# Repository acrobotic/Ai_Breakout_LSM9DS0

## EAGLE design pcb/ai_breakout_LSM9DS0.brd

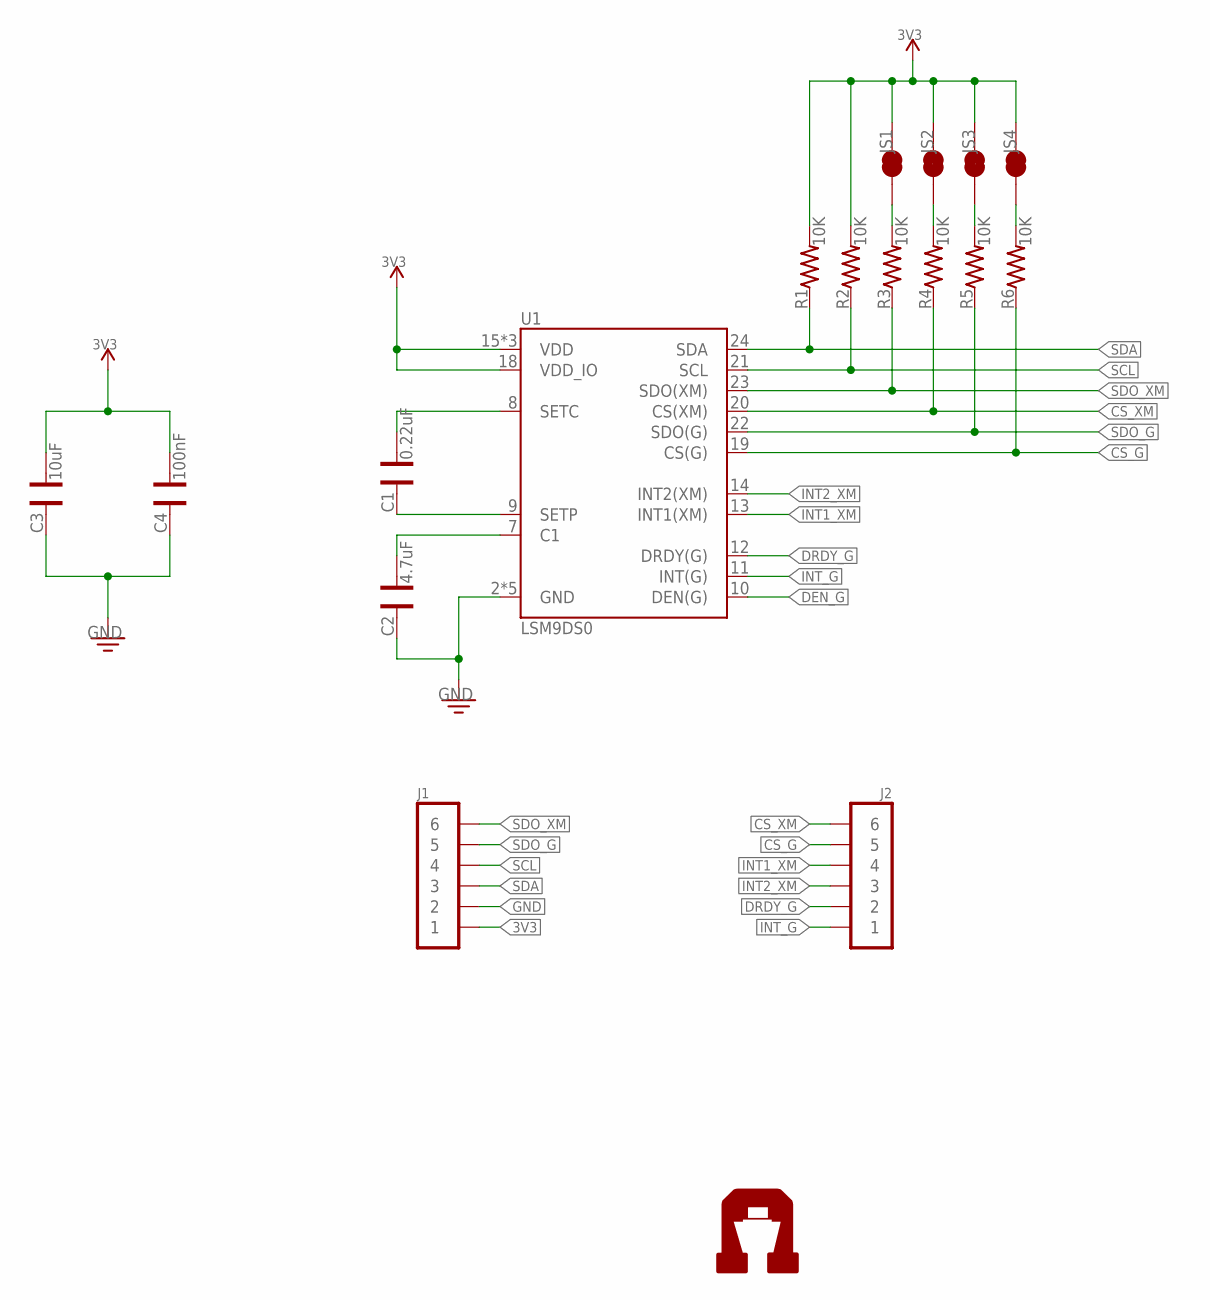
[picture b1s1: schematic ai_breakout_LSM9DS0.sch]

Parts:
C1: 0.22uF; CAP-0603
C2: 4.7uF; CAP-0603
C3: 10uF; CAP-0603
C4: 100nF; CAP-0603
J1: 1X06
J2: 1X06NOFIRST; 1X06-NOFIRST
JS1, JS2, JS3, JS4: 1X02-SJ-NCT
R1, R2, R3, R4, R5, R6: 10K; RES-0603
U1: LSM9DS0; LGA-24
U$4: AI-LOGOXS; AI-LOGO-XS

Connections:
3V3: C3.1, C4.1, J1.1, JS1.2, JS2.2, JS3.2, JS4.2, R1.2, R2.2, U1.15 (VDD), U1.16 (VDD), U1.17 (VDD), U1.18 (VDD_IO)
CS_G: J2.5, R6.1, U1.19 (CS(G))
CS_XM: J2.6, R4.1, U1.20 (CS(XM))
DEN_G: U1.10 (DEN(G))
DRDY_G: J2.2, U1.12 (DRDY(G))
GND: C2.2, C3.2, C4.2, J1.2, U1.2 (GND), U1.3 (GND), U1.4 (GND), U1.5 (GND), U1.6 (GND)
INT1_XM: J2.4, U1.13 (INT1(XM))
INT2_XM: J2.3, U1.14 (INT2(XM))
INT_G: J2.1, U1.11 (INT(G))
unnamed: C1.1, U1.8 (SETC)
unnamed: C1.2, U1.9 (SETP)
unnamed: C2.1, U1.7 (C1)
unnamed: JS1.1, R3.2
unnamed: JS2.1, R4.2
unnamed: JS3.1, R5.2
unnamed: JS4.1, R6.2
SCL: J1.4, R2.1, U1.21 (SCL)
SDA: J1.3, R1.1, U1.24 (SDA)
SDO_G: J1.5, R5.1, U1.22 (SDO(G))
SDO_XM: J1.6, R3.1, U1.23 (SDO(XM))

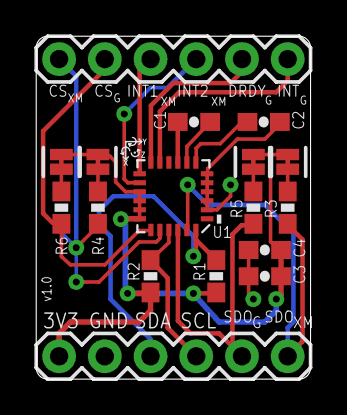
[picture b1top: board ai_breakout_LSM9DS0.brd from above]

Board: 2 copper layers, 15.2 x 19.1 mm, 18 parts (1 on the bottom side), 19 nets.

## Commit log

2014-10-17 ready for manufacturing
2014-10-19 minor
2014-10-20 fab done

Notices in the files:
parts and their libraries:
SparkFun-DigitalIC: Licensing: Creative Commons ShareAlike 4.0 International - https://creativecommons.org/licenses/by-sa/4.0
